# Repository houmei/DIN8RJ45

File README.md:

# DIN8RJ45 - DigitalRGB DIN8P connector to VGA-RJ45 converter (KiCad5)

Schematic

PCB

## 説明

[DIN8RJ45V01L04 デジタルRGBをVGA RJ45コネクタに変換](http://blog.livedoor.jp/hardyboy/archives/10203256.html "まごころせいじつ堂")  
<!-- [SORD m5用ROM/RAMカートリッジ基板](https://keisanki.booth.pm/items/3939000 "booth")  -->

## 履歴
V01L01(非公開) 初版 RJ45のフットプリントミス  
V01L02(非公開) RJ45のフットプリントミス  
V01L03(非公開) RJ45のフットプリントミス ヤンナルネ  
V01L04 正常動作確認  

## DIN8RJ45V01L04GB - Gerber
JLCPCBなどにそのまま出図可能です。

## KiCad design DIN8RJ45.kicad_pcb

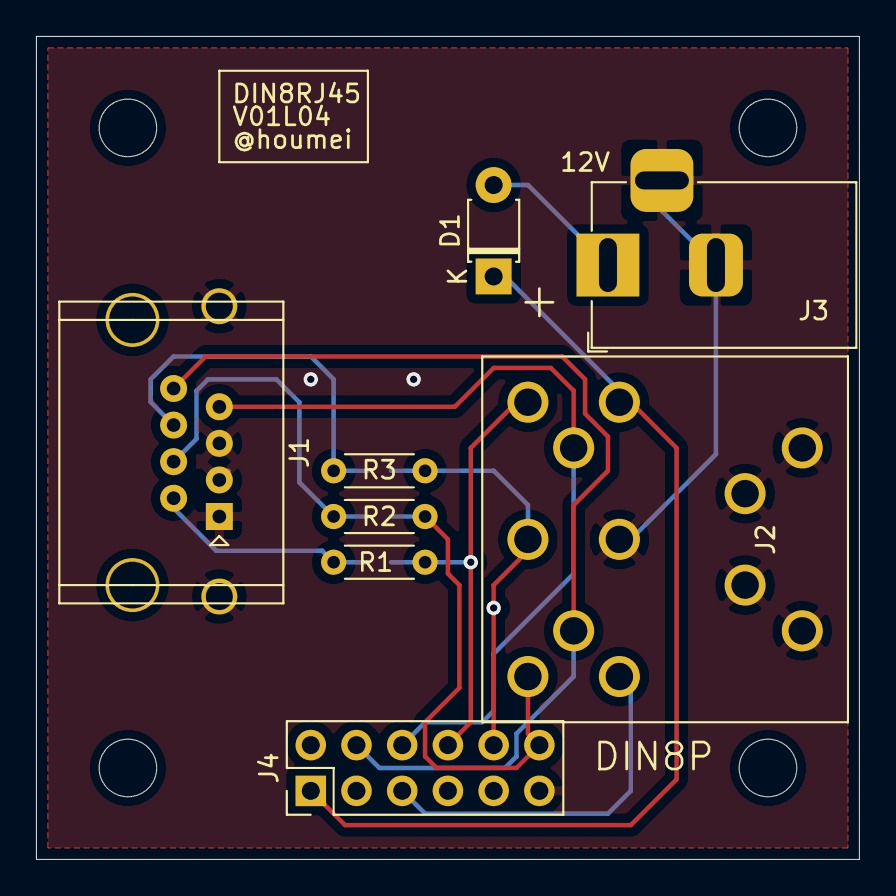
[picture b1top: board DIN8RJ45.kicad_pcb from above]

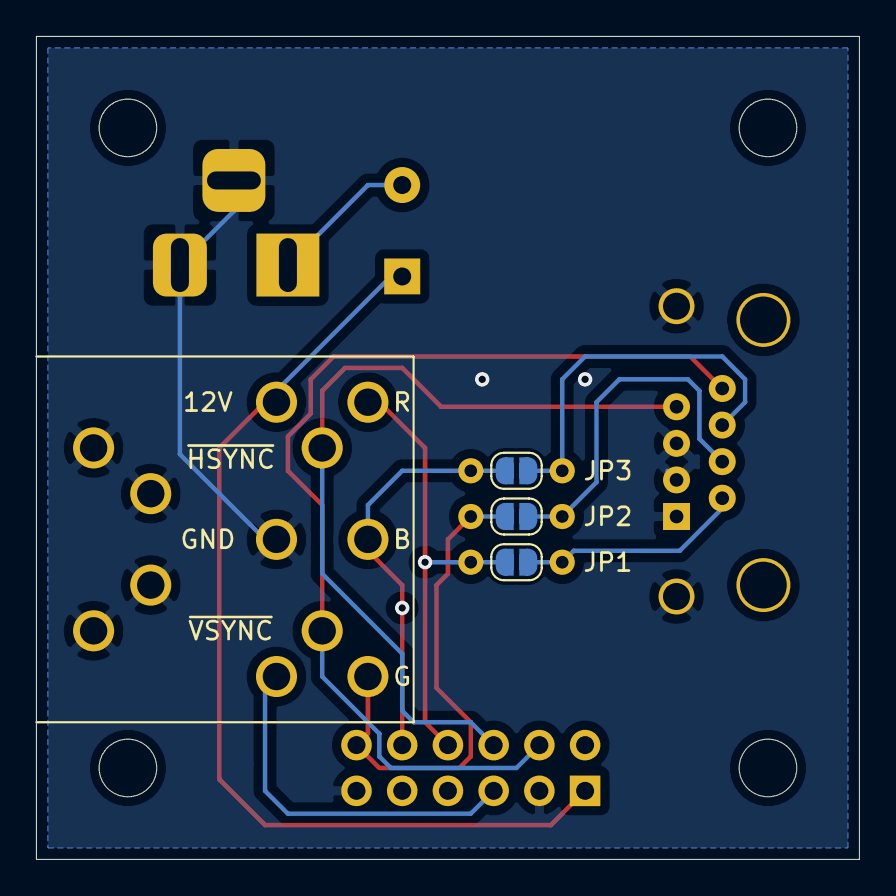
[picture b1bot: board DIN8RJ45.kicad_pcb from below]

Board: 2 copper layers, 45.7 x 45.7 mm, 11 parts (3 on the bottom side), 12 nets.

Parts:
D1: D; D_T-1_P5.08mm_Horizontal
J1: RJ45; RJ45_7810-8P8C
J2: DIN-8; DIN8P
J3: Barrel_Jack_Switch; BarrelJack_Horizontal
J4: Conn_02x06_Odd_Even; PinHeader_2x06_P2.54mm_Vertical
JP1, JP2, JP3: SJ2O; SolderJumper-2_P1.3mm_Open_RoundedPad1.0x1.5mm
R1, R2, R3: 150; R_Axial_DIN0204_L3.6mm_D1.6mm_P5.08mm_Horizontal

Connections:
12V: D1.1, J2.1, J4.1
/B6: J1.6, JP3.1, R3.2
/G4: J1.4, JP2.1, R2.2
/R2: J1.2, JP1.1, R1.2
BLUE: J2.8, J4.10, JP3.2, R3.1
GND: J1.1, J1.3, J1.5, J2.2, J3.2, J3.3, J4.3, J4.11
GREEN: J2.7, J4.12, JP2.2, R2.1
INT: J2.3, J4.5
unnamed: D1.2, J3.1
RED: J2.6, J4.8, JP1.2, R1.1
~HS: J1.7, J2.4, J4.6
~VS: J1.8, J2.5, J4.4

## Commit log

2022-12-23 add local library
